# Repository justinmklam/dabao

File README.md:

# dabao

打包 (dǎ bāo or daa2 baau1), which means to take out (food) in Chinese, is a wireless, portable 36-key keyboard with a thumb trackpoint, designed for maximum flexibility and convenience.

> 
> <sub>Keyboard can be used as a unibody...</sub>
>
> 
> <sub>... or as a split!</sub>

## Design Rationale

I found that split keyboards can be cumbersome when I’m not working at a desk. Managing two independent halves (as well as a laptop) while moving between coworking spaces, cafés, or even working from the couch quickly becomes unwieldy, and I thought there had to be a better way.

This project explores a keyboard that can seamlessly switch between a unibody form factor (easy to pick up and carry) and a fully split configuration when there's space for a full ergonomic setup. An integrated pointing device is included to reduce the need for external peripherals, making it truly portable.

Albeit unconventional, the trackpoint is positioned under the thumb to:

- Enable the use of hotswap sockets while keeping the overall keyboard height low
- Eliminate the need to modify keycaps for trackpoint clearance
- Allow the fingers to remain on the home row during pointing tasks

In practice, using the thumb instead of the index finger feels functionally similar. After a short adjustment period, I personally haven't experienced a meaningful loss in accuracy or precision.

## Features

- **Unibody or Split:** Unique magnetic 4-pin connector allows the keyboard to be used as a single unibody or split into two halves via a USB-C cable. Use unibody mode on the go, and split mode at your desk!
- **Single Microcontroller:** Uses one microcontroller and a GPIO expander, eliminating the need for two controllers or batteries to reduce costs and avoid managing uneven battery discharge.
- **Integrated Trackpoint:** For convenient and precise cursor control.
- **Reversible PCB:** Keeps ordering PCBs affordable. Also enables the trackpoint to be installed on the left or right side.
- **Wireless:** Wireless operation (between the host computer) for portability.
- **Hotswap Switches:** Supports Choc V1 or V2 switches. Can also be soldered directly if desired.

## Firmware

See [zmk-config](https://github.com/justinmklam/zmk-config).

## Case

*Coming soon!* - The case will make the magnetic interface more robust, which will allow the keyboard to be lifted from either side without it collapsing in half. Additional magnets will likely be added to make the connection more secure.

## Build Guide

> [!WARNING]
> This project is provided for educational and experimental purposes only. It is shared "as-is," without any warranty of any kind, express or implied, including but not limited to the warranties of merchantability or fitness for a particular purpose. By using these files, you acknowledge that you are assuming all risks associated with the assembly, use, and operation of the hardware. The author shall not be liable for any claim, damages, or other liability, whether in an action of contract, tort, or otherwise, arising from, out of, or in connection with the project or the use of these files.

*Coming soon!*

## Acknowledgements

This design was inspired by the following keyboards:

- [TPS42](https://github.com/crehmann/TPS42)
- [duet](https://github.com/zzeneg/duet)
- [Santoku](https://www.reddit.com/r/ErgoMechKeyboards/comments/oisnad/i_made_this_santoku_gen_2_trackpoint_as_a/?chainedPosts=t3_g4m3f6)

Helpful trackpoint resources:

- [infused-kim's Trackpoint Driver](https://github.com/infused-kim/kb_zmk_ps2_mouse_trackpoint_driver) - outdated for the recent versions of zmk, but still a treasure trove of information
- [Jorne Trackpoint Wiki](https://github.com/joric/jorne/wiki/Tracking)
- [TheMK Wiki - TrackPoint Overview](https://wiki.themk.org/index.php/TrackPoint)
- [KBD News - Trackpoint Integration Guide](https://kbd.news/How-to-integrate-a-trackpoint-into-your-keyboard-2447.html)
- [r/Trackpoint_Builders](https://www.reddit.com/r/TrackPoint_Builders/)
- [Trackpoint Builders Discord](https://discord.gg/48gM4jZkW)

## Support

Thank you to my sponsors for making this project possible!

The PCBs for this project were manufactured by **[PCBWay](https://pcbway.com)**. The boards came out clean with good tolerances and had a fast turnaround, especially considering it came from the other side of the world. Recommended if you're looking to prototype or build your own keyboard!

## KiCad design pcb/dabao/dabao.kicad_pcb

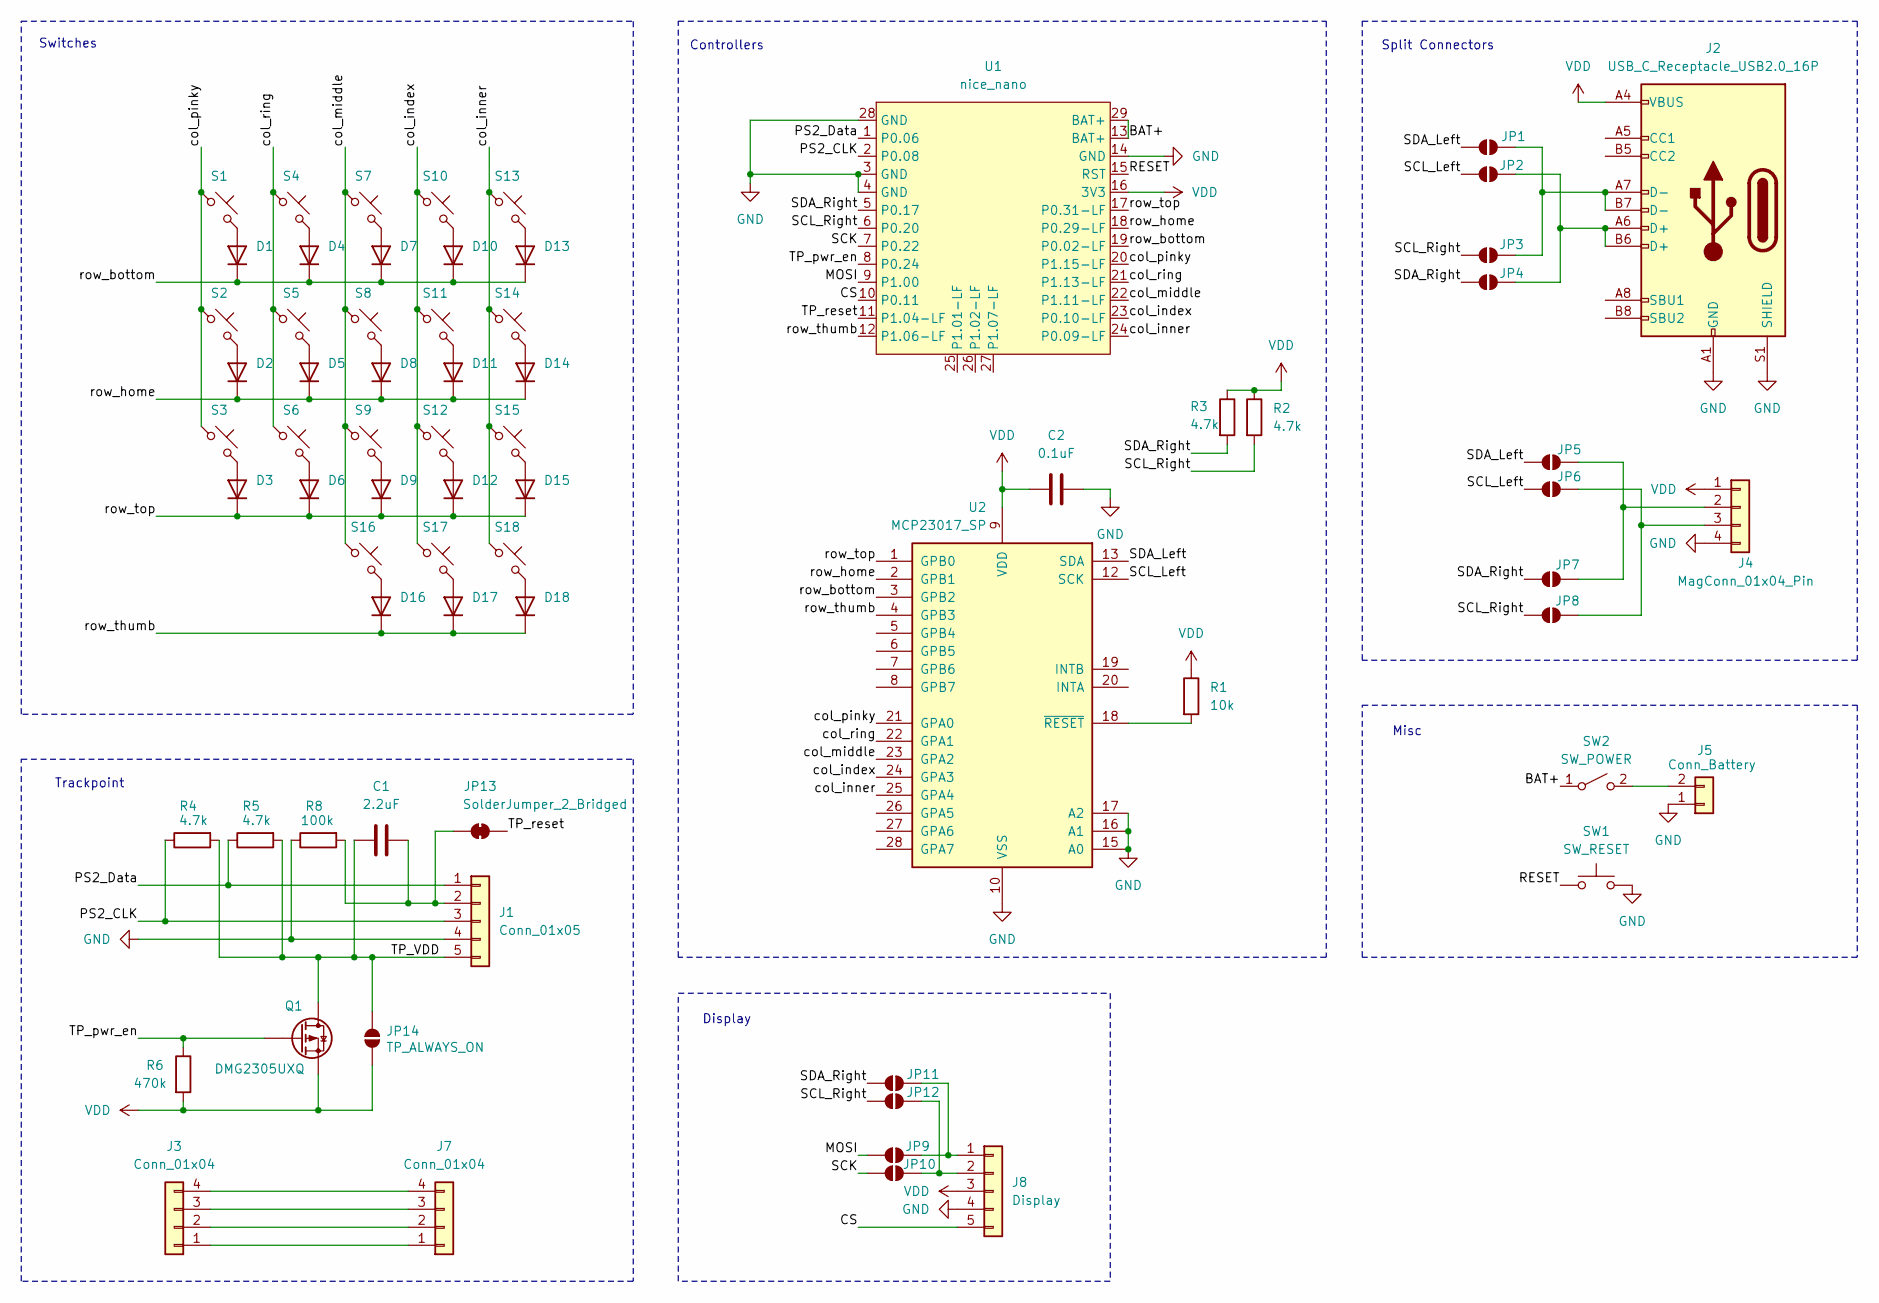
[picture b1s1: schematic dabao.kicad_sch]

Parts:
C1: 2.2uF; C_0805_2012Metric
C2: 0.1uF; C_0805_2012Metric
D1, D2, D3, D4, D5, D6, D7, D8, D9, D10, D11, D12, D13, D14, D15, D16, D17, D18: 1N4148; D_SOD-323_HandSoldering_Reversable
J1: Conn_01x05; TPModule
J2: USB_C_Receptacle_USB2.0_16P; USB_C_Receptacle_GCT_USB4085
J3, J7: Conn_01x04; TPSensorModule_Connector
J4: MagConn_01x04_Pin; PinMagnetic_1x04_P2.54mm
J5: Conn_Battery; JST_PH_S2B-PH-K_1x02_P2.00mm_Horizontal
J8: Display; PinHeader_1x05_P2.54mm_Vertical
JP1, JP2, JP3, JP4, JP5, JP6, JP7, JP8, JP9, JP10, JP11, JP12: SolderJumper_2_Open; SolderJumper-2_P1.3mm_Open_TrianglePad1.0x1.5mm
JP13: SolderJumper_2_Bridged; SolderJumper-2_P1.3mm_Bridged_Pad1.0x1.5mm
JP14: TP_ALWAYS_ON; SolderJumper-2_P1.3mm_Open_TrianglePad1.0x1.5mm
Q1: DMG2305UXQ
R1: 10k; R_0805_2012Metric
R2, R3, R4, R5: 4.7k; R_0805_2012Metric
R6: 470k; R_0805_2012Metric
R8: 100k; R_0805_2012Metric
S1, S2, S3, S4, S5, S6, S7, S8, S9, S10, S11, S12, S13, S14, S15, S16, S17, S18: choc_v1_SW_HS; Kailh_socket_PG1350_optional_reversible.kicad_mod
SW1: SW_RESET; SW_Push_SPST_NO_Alps_SKRK
SW2: SW_POWER; SW_MSK12C02-HB
U1: nice_nano; nice_nano_AH_USBup
U2: MCP23017_SP; SOIC-28W_7.5x17.9mm_P1.27mm

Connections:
/BAT+: SW2.1 (A), U1.13 (BAT+), U1.29 (BAT+)
/CS: J8.5, U1.10 (P0.11)
/MOSI: JP9.1 (A), U1.9 (P1.00)
/PS2_CLK: J1.3, R4.1, U1.2 (P0.08)
/PS2_Data: J1.1, R5.1, U1.1 (P0.06)
/RESET: SW1.1, U1.15 (RST)
/SCK: JP10.1 (A), U1.7 (P0.22)
/SCL_Left: JP2.1 (A), JP6.1 (A), U2.12 (SCK)
/SCL_Right: JP3.1 (A), JP8.1 (A), JP12.1 (A), R2.2, U1.6 (P0.20)
/SDA_Left: JP1.1 (A), JP5.1 (A), U2.13 (SDA)
/SDA_Right: JP4.1 (A), JP7.1 (A), JP11.1 (A), R3.2, U1.5 (P0.17)
/TP_VDD: C1.1, J1.5, JP14.2 (B), Q1.D, R4.2, R5.2
/TP_pwr_en: Q1.G, R6.1, U1.8 (P0.24)
/TP_reset: JP13.2 (B), U1.11 (P1.04-LF)
/col_index: S10.1, S11.1, S12.1, S17.1, U1.23 (P0.10-LF), U2.24 (GPA3)
/col_inner: S13.1, S14.1, S15.1, S18.1, U1.24 (P0.09-LF), U2.25 (GPA4)
/col_middle: S7.1, S8.1, S9.1, S16.1, U1.22 (P1.11-LF), U2.23 (GPA2)
/col_pinky: S1.1, S2.1, S3.1, U1.20 (P1.15-LF), U2.21 (GPA0)
/col_ring: S4.1, S5.1, S6.1, U1.21 (P1.13-LF), U2.22 (GPA1)
/row_bottom: D1.1 (K), D4.1 (K), D7.1 (K), D10.1 (K), D13.1 (K), U1.19 (P0.02-LF), U2.3 (GPB2)
/row_home: D2.1 (K), D5.1 (K), D8.1 (K), D11.1 (K), D14.1 (K), U1.18 (P0.29-LF), U2.2 (GPB1)
/row_thumb: D16.1 (K), D17.1 (K), D18.1 (K), U1.12 (P1.06-LF), U2.4 (GPB3)
/row_top: D3.1 (K), D6.1 (K), D9.1 (K), D12.1 (K), D15.1 (K), U1.17 (P0.31-LF), U2.1 (GPB0)
GND: C2.2, J1.4, J2.A1 (GND), J2.A12 (GND), J2.B1 (GND), J2.B12 (GND), J2.S1 (SHIELD), J4.4, J5.1, J8.4, R8.1, SW1.2, U1.3 (GND), U1.4 (GND), U1.14 (GND), U1.28 (GND), U2.10 (VSS), U2.15 (A0), U2.16 (A1), U2.17 (A2)
unnamed: D1.2 (A), S1.2
unnamed: D2.2 (A), S2.2
unnamed: D3.2 (A), S3.2
unnamed: D4.2 (A), S4.2
unnamed: D5.2 (A), S5.2
unnamed: D6.2 (A), S6.2
unnamed: D7.2 (A), S7.2
unnamed: D8.2 (A), S8.2
unnamed: D9.2 (A), S9.2
unnamed: D10.2 (A), S10.2
unnamed: D11.2 (A), S11.2
unnamed: D12.2 (A), S12.2
unnamed: D13.2 (A), S13.2
unnamed: D14.2 (A), S14.2
unnamed: D15.2 (A), S15.2
unnamed: D16.2 (A), S16.2
unnamed: D17.2 (A), S17.2
unnamed: D18.2 (A), S18.2
unnamed: C1.2, J1.2, JP13.1 (A), R8.2
unnamed: J3.1, J7.1
unnamed: J3.2, J7.2
unnamed: J3.3, J7.3
unnamed: J3.4, J7.4
unnamed: J4.2, JP5.2 (B), JP7.2 (B)
unnamed: J4.3, JP6.2 (B), JP8.2 (B)
unnamed: J5.2, SW2.2 (B)
unnamed: J8.1, JP9.2 (B), JP11.2 (B)
unnamed: J8.2, JP10.2 (B), JP12.2 (B)
unnamed: J2.A7 (D-), J2.B7 (D-), JP1.2 (B), JP3.2 (B)
unnamed: J2.A6 (D+), J2.B6 (D+), JP2.2 (B), JP4.2 (B)
unnamed: R1.2, U2.18 (~RESET)
VDD: C2.1, J2.A4 (VBUS), J2.A9 (VBUS), J2.B4 (VBUS), J2.B9 (VBUS), J4.1, J8.3, JP14.1 (A), Q1.S, R1.1, R2.1, R3.1, R6.2, U1.16 (3V3), U2.9 (VDD)

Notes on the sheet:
Misc
Display
Trackpoint
Split Connectors
Controllers
Switches

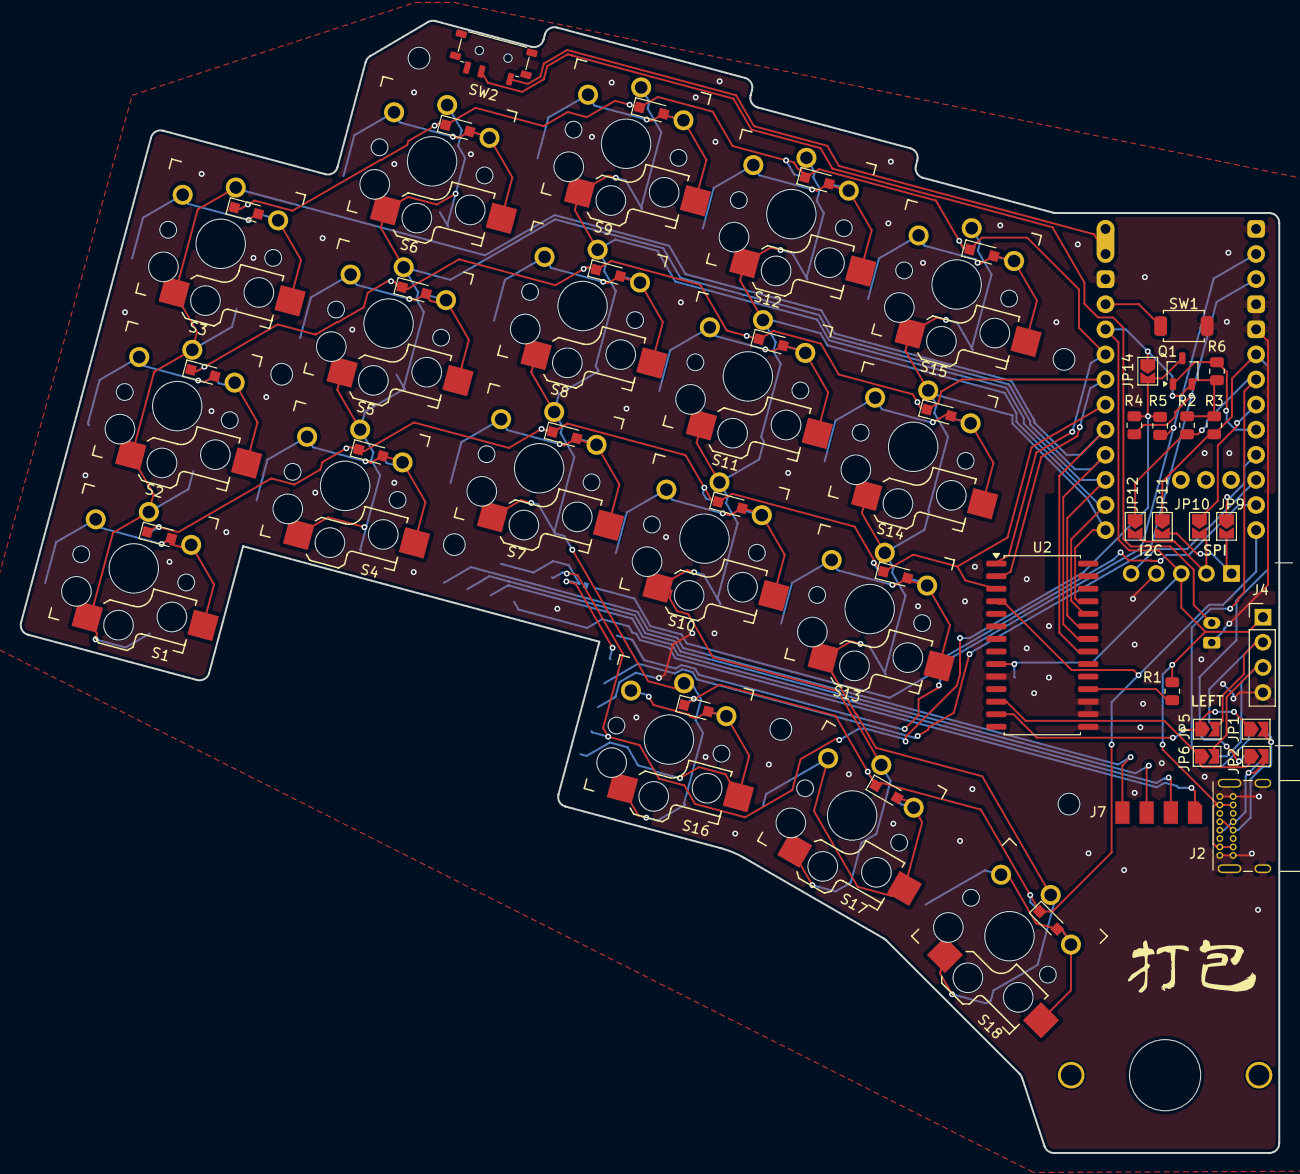
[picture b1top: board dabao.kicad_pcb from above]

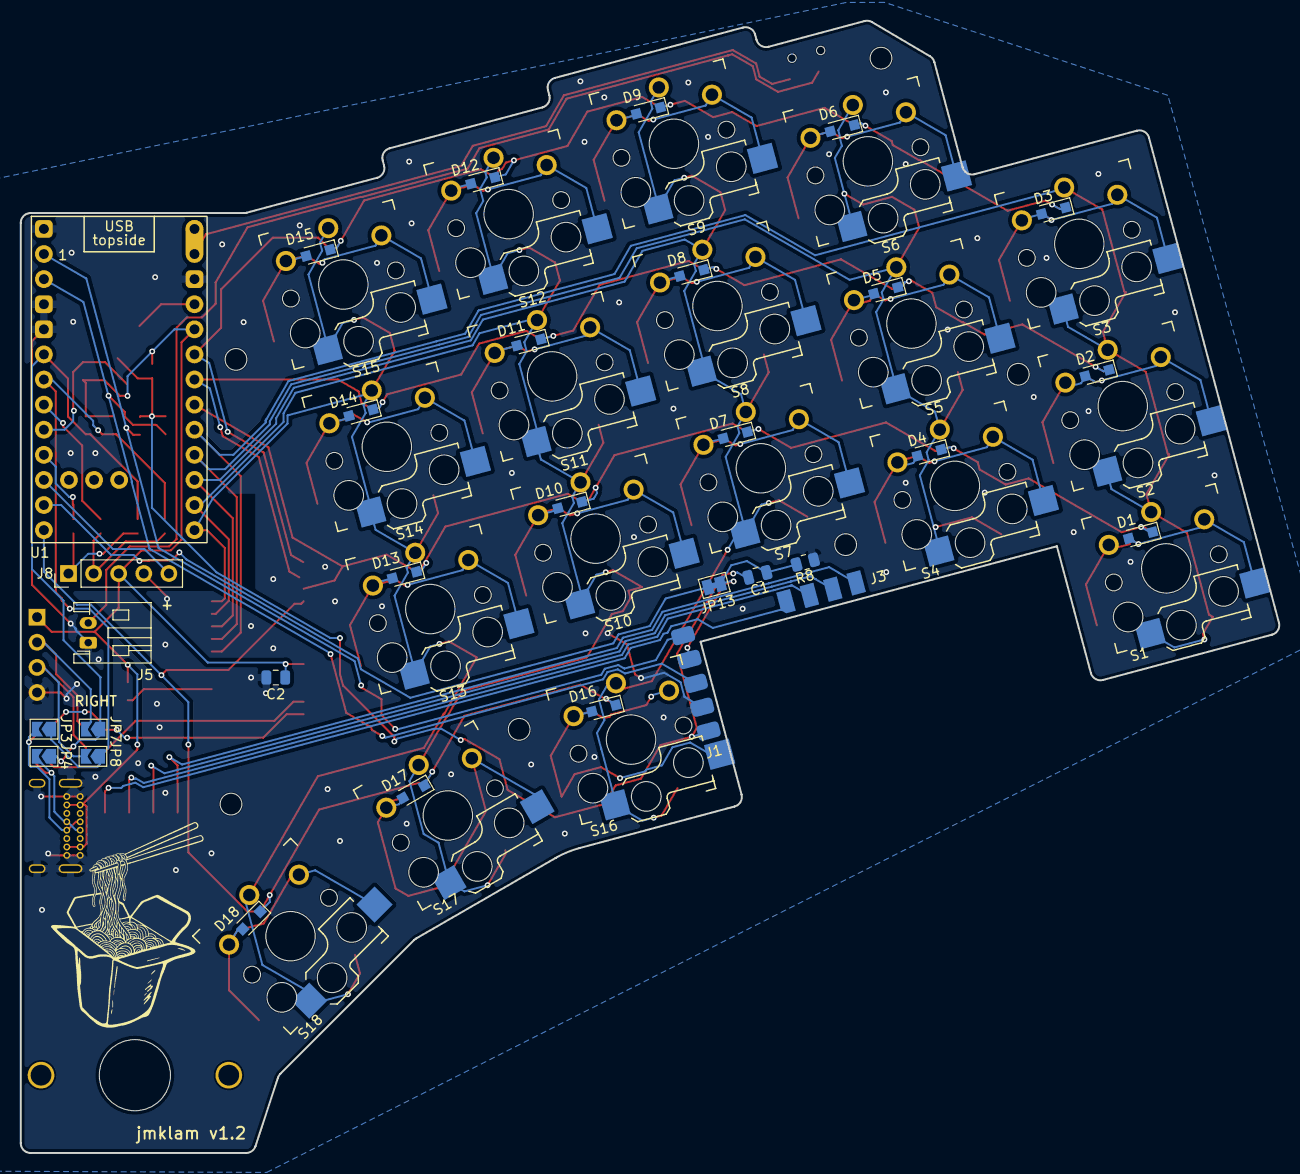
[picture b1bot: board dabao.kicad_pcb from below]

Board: 2 copper layers, 127.4 x 114.6 mm, 71 parts (49 on the bottom side), 56 nets.

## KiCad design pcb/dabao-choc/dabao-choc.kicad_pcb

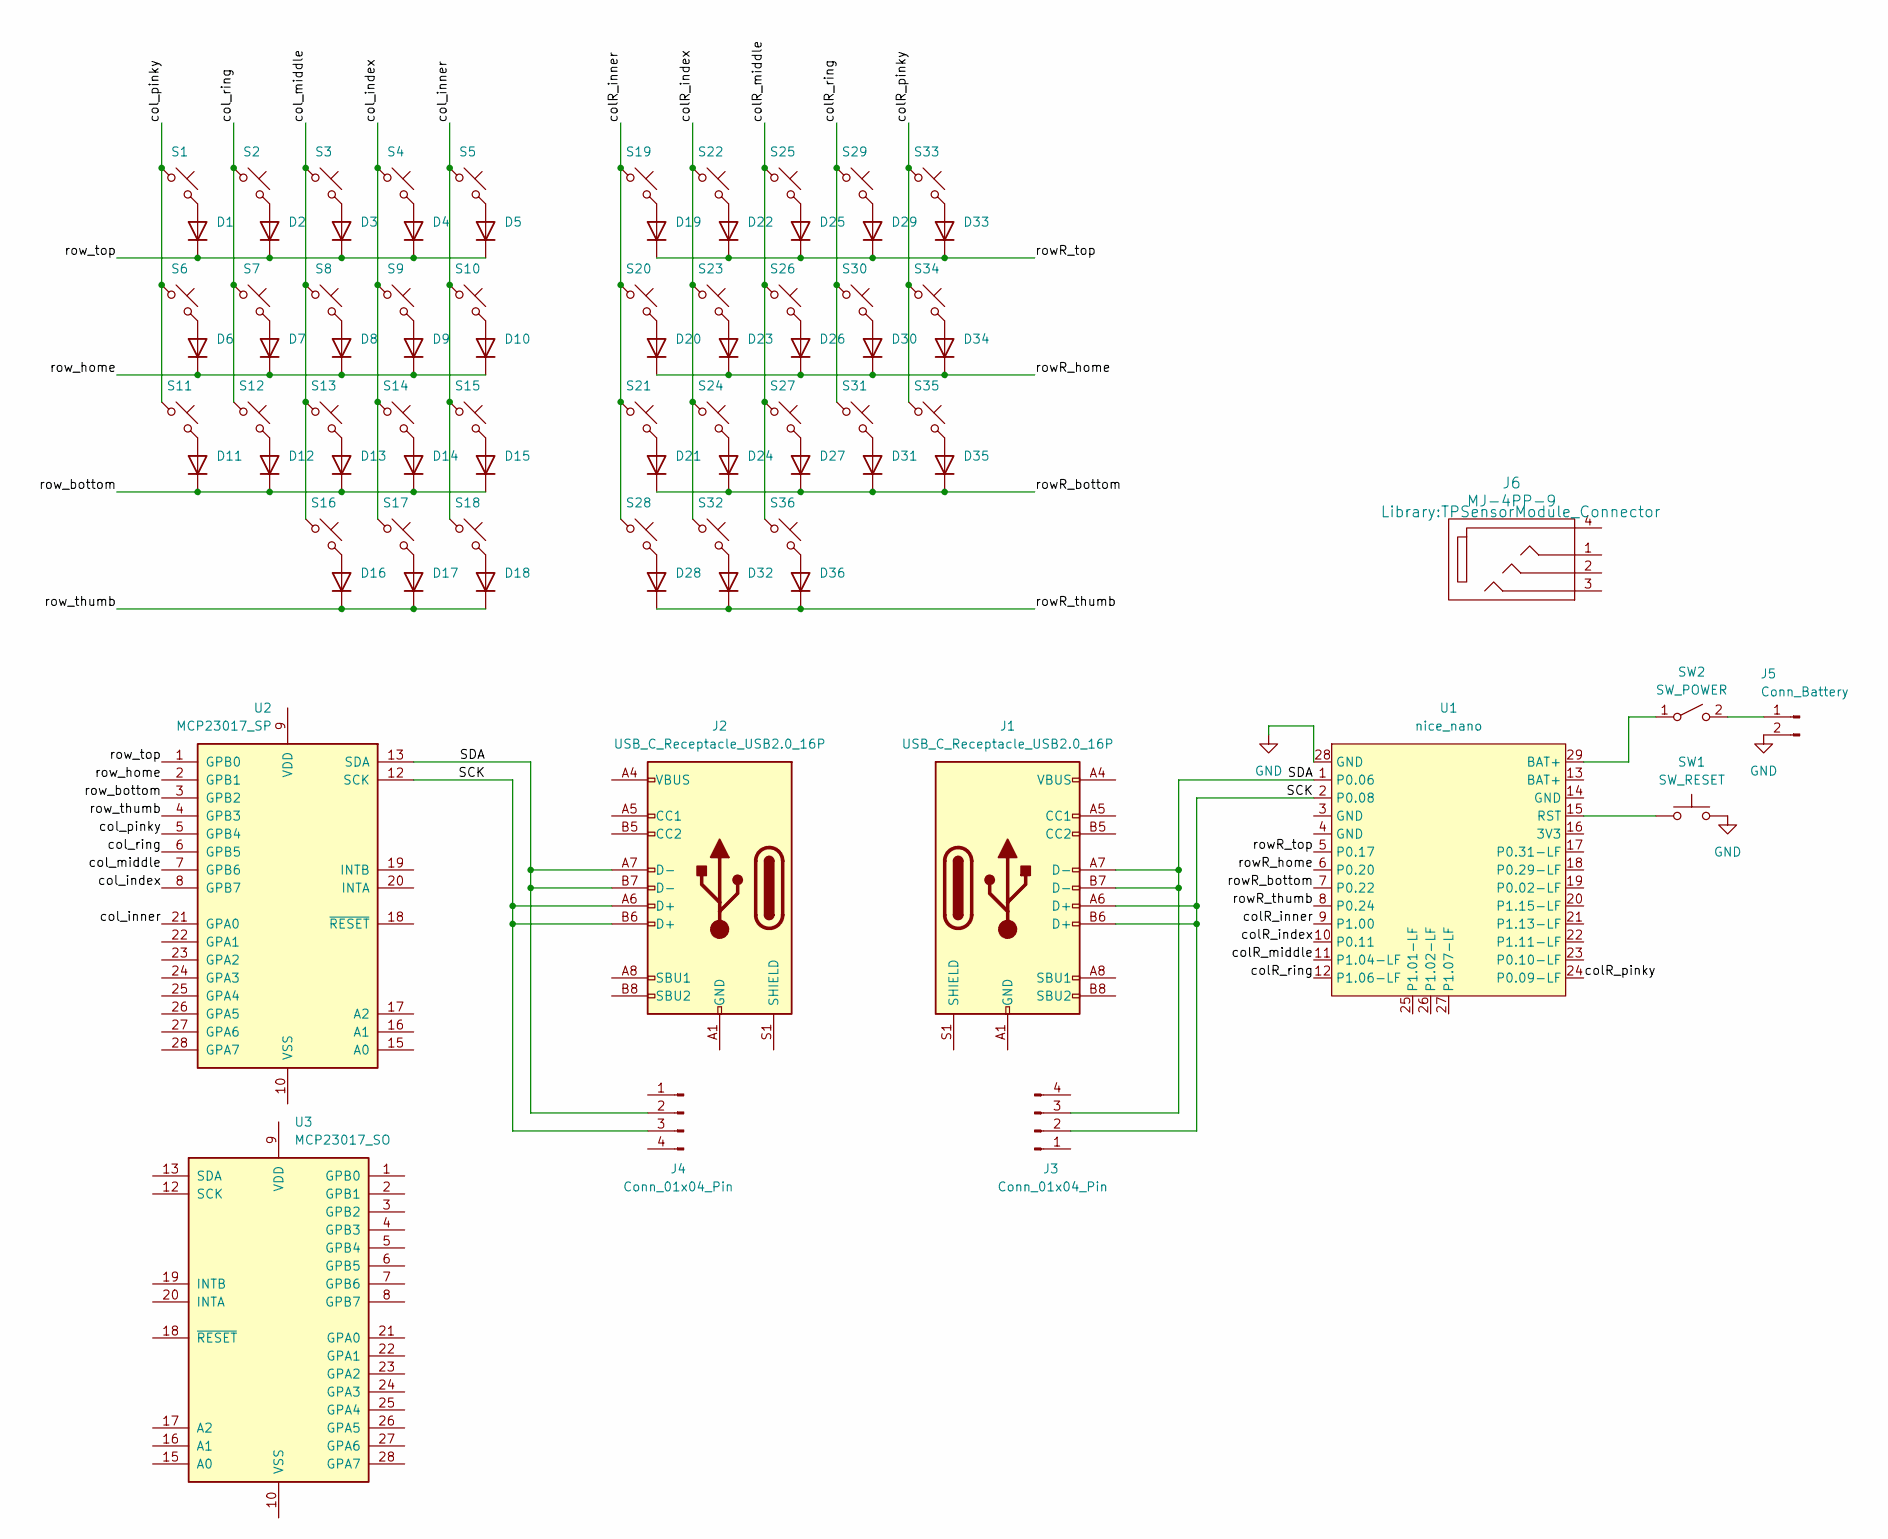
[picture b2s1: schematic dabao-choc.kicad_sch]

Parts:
D1, D2, D3, D4, D5, D6, D7, D8, D9, D10, D11, D12, D13, D14, D15, D16, D17, D18, D19, D20, D21, D22, D23, D24, D25, D26, D27, D28, D29, D30, D31, D32, D33, D34, D35, D36: 1N4148; D_DO-35_SOD27_P7.62mm_Horizontal
J1, J2: USB_C_Receptacle_USB2.0_16P; USB_C_Receptacle_GCT_USB4085
J3, J4: Conn_01x04_Pin; PinMagnetic_1x04_P2.54mm
J5: Conn_Battery; JST_EH_S2B-EH_1x02_P2.50mm_Horizontal
J6: MJ-4PP-9; TPSensorModule_Connector
S1, S2, S3, S4, S5, S6, S7, S8, S9, S10, S11, S12, S13, S14, S15, S16, S17, S18, S19, S20, S21, S22, S23, S24, S25, S26, S27, S28, S29, S30, S31, S32, S33, S34, S35, S36: choc_v1_SW_HS; SW_choc_v1_HS_CPG135001S30_1u
SW1: SW_RESET; SW_Push_SPST_NO_Alps_SKRK
SW2: SW_POWER; SW_MSK12C02-HB
U1: nice_nano; nice_nano_AH_USBup
U2: MCP23017_SP; DIP-28_W7.62mm
U3: MCP23017_SO; SOIC-28W_7.5x17.9mm_P1.27mm

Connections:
/colR_index: S22.1, S23.1, S24.1, S32.1, U1.10 (P0.11)
/colR_inner: S19.1, S20.1, S21.1, S28.1, U1.9 (P1.00)
/colR_middle: S25.1, S26.1, S27.1, S36.1, U1.11 (P1.04-LF)
/colR_pinky: S33.1, S34.1, S35.1, U1.24 (P0.09-LF)
/colR_ring: S29.1, S30.1, S31.1, U1.12 (P1.06-LF)
/col_index: S4.1, S9.1, S14.1, S17.1, U2.8 (GPB7)
/col_inner: S5.1, S10.1, S15.1, S18.1, U2.21 (GPA0)
/col_middle: S3.1, S8.1, S13.1, S16.1, U2.7 (GPB6)
/col_pinky: S1.1, S6.1, S11.1, U2.5 (GPB4)
/col_ring: S2.1, S7.1, S12.1, U2.6 (GPB5)
/rowR_bottom: D21.1 (K), D24.1 (K), D27.1 (K), D31.1 (K), D35.1 (K), U1.7 (P0.22)
/rowR_home: D20.1 (K), D23.1 (K), D26.1 (K), D30.1 (K), D34.1 (K), U1.6 (P0.20)
/rowR_thumb: D28.1 (K), D32.1 (K), D36.1 (K), U1.8 (P0.24)
/rowR_top: D19.1 (K), D22.1 (K), D25.1 (K), D29.1 (K), D33.1 (K), U1.5 (P0.17)
/row_bottom: D11.1 (K), D12.1 (K), D13.1 (K), D14.1 (K), D15.1 (K), U2.3 (GPB2)
/row_home: D6.1 (K), D7.1 (K), D8.1 (K), D9.1 (K), D10.1 (K), U2.2 (GPB1)
/row_thumb: D16.1 (K), D17.1 (K), D18.1 (K), U2.4 (GPB3)
/row_top: D1.1 (K), D2.1 (K), D3.1 (K), D4.1 (K), D5.1 (K), U2.1 (GPB0)
GND: J5.2, SW1.2, U1.28 (GND)
unnamed: D1.2 (A), S1.2
unnamed: D2.2 (A), S2.2
unnamed: D3.2 (A), S3.2
unnamed: D4.2 (A), S4.2
unnamed: D5.2 (A), S5.2
unnamed: D6.2 (A), S6.2
unnamed: D7.2 (A), S7.2
unnamed: D8.2 (A), S8.2
unnamed: D9.2 (A), S9.2
unnamed: D10.2 (A), S10.2
unnamed: D11.2 (A), S11.2
unnamed: D12.2 (A), S12.2
unnamed: D13.2 (A), S13.2
unnamed: D14.2 (A), S14.2
unnamed: D15.2 (A), S15.2
unnamed: D16.2 (A), S16.2
unnamed: D17.2 (A), S17.2
unnamed: D18.2 (A), S18.2
unnamed: D19.2 (A), S19.2
unnamed: D20.2 (A), S20.2
unnamed: D21.2 (A), S21.2
unnamed: D22.2 (A), S22.2
unnamed: D23.2 (A), S23.2
unnamed: D24.2 (A), S24.2
unnamed: D25.2 (A), S25.2
unnamed: D26.2 (A), S26.2
unnamed: D27.2 (A), S27.2
unnamed: D28.2 (A), S28.2
unnamed: D29.2 (A), S29.2
unnamed: D30.2 (A), S30.2
unnamed: D31.2 (A), S31.2
unnamed: D32.2 (A), S32.2
unnamed: D33.2 (A), S33.2
unnamed: D34.2 (A), S34.2
unnamed: D35.2 (A), S35.2
unnamed: D36.2 (A), S36.2
unnamed: J1.A1 (GND), J1.A12 (GND), J1.B1 (GND), J1.B12 (GND)
unnamed: J1.A4 (VBUS), J1.A9 (VBUS), J1.B4 (VBUS), J1.B9 (VBUS)
unnamed: J2.A1 (GND), J2.A12 (GND), J2.B1 (GND), J2.B12 (GND)
unnamed: J2.A4 (VBUS), J2.A9 (VBUS), J2.B4 (VBUS), J2.B9 (VBUS)
unnamed: J5.1, SW2.2 (B)
unnamed: SW2.1 (A), U1.29 (BAT+)
unnamed: SW1.1, U1.15 (RST)

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
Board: 2 copper layers, 93 parts (76 on the bottom side), 66 nets, no tracks yet.

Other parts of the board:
MH1, MH2, MH3, MH4, MH5, MH6, MH7, MH8, MH9, MH10: mounting_hole_npth

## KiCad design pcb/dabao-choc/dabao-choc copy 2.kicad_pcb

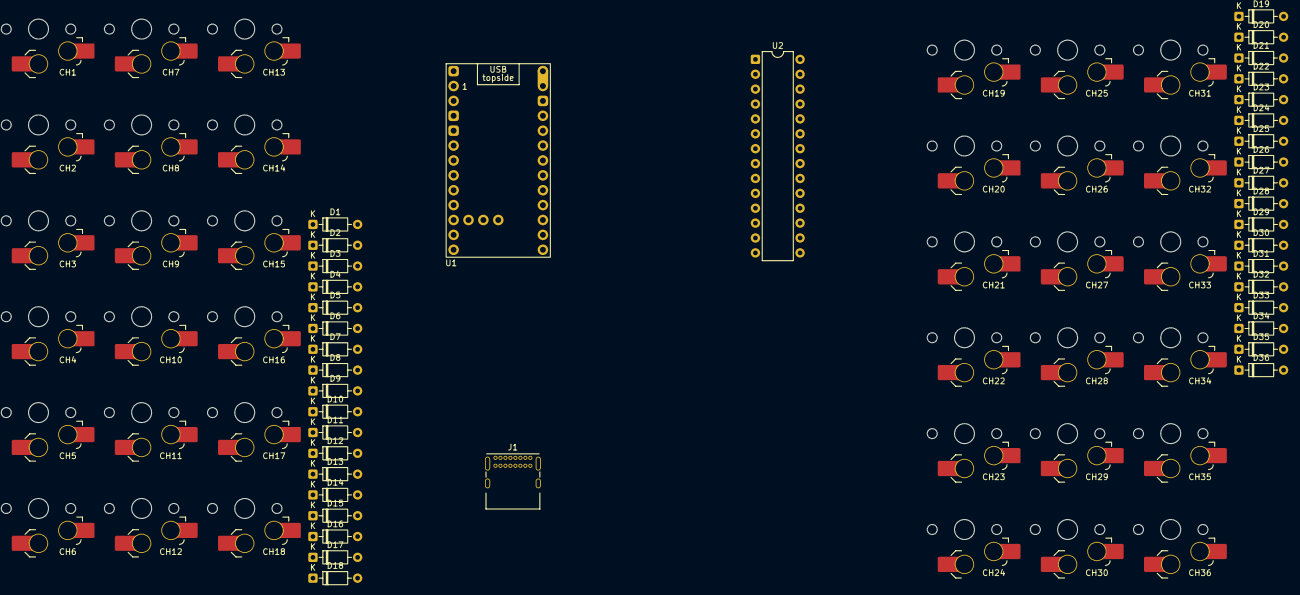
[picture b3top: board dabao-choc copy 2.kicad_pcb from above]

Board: 2 copper layers, 75 parts (0 on the bottom side), 56 nets, no tracks yet.

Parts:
CH1, CH2, CH3, CH4, CH5, CH6, CH7, CH8, CH9, CH10, CH11, CH12, CH13, CH14, CH15, CH16, CH17, CH18, CH19, CH20, CH21, CH22, CH23, CH24, CH25, CH26, CH27, CH28, CH29, CH30, CH31, CH32, CH33, CH34, CH35, CH36: choc_v1_SW_HS; SW_choc_v1_HS_CPG135001S30_1u
D1, D2, D3, D4, D5, D6, D7, D8, D9, D10, D11, D12, D13, D14, D15, D16, D17, D18, D19, D20, D21, D22, D23, D24, D25, D26, D27, D28, D29, D30, D31, D32, D33, D34, D35, D36: 1N4148; D_DO-35_SOD27_P7.62mm_Horizontal
J1: USB_C_Receptacle_USB2.0_16P; USB_C_Receptacle_GCT_USB4085
U1: nice_nano; nice_nano_AH_USBup
U2: MCP23017_SP; DIP-28_W7.62mm

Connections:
/col_index: CH4.1, CH9.1, CH14.1, CH17.1
/col_inner: CH5.1, CH10.1, CH15.1, CH18.1
/col_middle: CH3.1, CH8.1, CH13.1, CH16.1
/col_pinky: CH1.1, CH6.1, CH11.1
/col_ring: CH2.1, CH7.1, CH12.1
/row_bottom: D11.1 (K), D12.1 (K), D13.1 (K), D14.1 (K), D15.1 (K)
/row_home: D6.1 (K), D7.1 (K), D8.1 (K), D9.1 (K), D10.1 (K)
/row_thumb: D16.1 (K), D17.1 (K), D18.1 (K)
/row_top: D1.1 (K), D2.1 (K), D3.1 (K), D4.1 (K), D5.1 (K)
unnamed: CH19.1, CH20.1, CH21.1
unnamed: CH22.1, CH23.1, CH24.1
unnamed: CH25.1, CH26.1, CH27.1, CH28.1
unnamed: CH29.1, CH30.1, CH31.1, CH32.1
unnamed: CH33.1, CH34.1, CH35.1, CH36.1
unnamed: CH1.2, D1.2 (A)
unnamed: CH2.2, D2.2 (A)
unnamed: CH3.2, D3.2 (A)
unnamed: CH4.2, D4.2 (A)
unnamed: CH5.2, D5.2 (A)
unnamed: CH6.2, D6.2 (A)
unnamed: CH7.2, D7.2 (A)
unnamed: CH8.2, D8.2 (A)
unnamed: CH9.2, D9.2 (A)
unnamed: CH10.2, D10.2 (A)
unnamed: CH11.2, D11.2 (A)
unnamed: CH12.2, D12.2 (A)
unnamed: CH13.2, D13.2 (A)
unnamed: CH14.2, D14.2 (A)
unnamed: CH15.2, D15.2 (A)
unnamed: CH16.2, D16.2 (A)
unnamed: CH17.2, D17.2 (A)
unnamed: CH18.2, D18.2 (A)
unnamed: CH19.2, D19.2 (A)
unnamed: D19.1 (K), D22.1 (K), D25.1 (K), D29.1 (K), D33.1 (K)
unnamed: CH20.2, D20.2 (A)
unnamed: D20.1 (K), D23.1 (K), D26.1 (K), D30.1 (K), D34.1 (K)
unnamed: CH21.2, D21.2 (A)
unnamed: D21.1 (K), D24.1 (K), D27.1 (K), D31.1 (K), D35.1 (K)
unnamed: CH22.2, D22.2 (A)
unnamed: CH23.2, D23.2 (A)
unnamed: CH24.2, D24.2 (A)
unnamed: CH25.2, D25.2 (A)
unnamed: CH26.2, D26.2 (A)
unnamed: CH27.2, D27.2 (A)
unnamed: CH28.2, D28.2 (A)
unnamed: D28.1 (K), D32.1 (K), D36.1 (K)
unnamed: CH29.2, D29.2 (A)
unnamed: CH30.2, D30.2 (A)
unnamed: CH31.2, D31.2 (A)
unnamed: CH32.2, D32.2 (A)
unnamed: CH33.2, D33.2 (A)
unnamed: CH34.2, D34.2 (A)
unnamed: CH35.2, D35.2 (A)
unnamed: CH36.2, D36.2 (A)
unnamed: J1.A1 (GND), J1.A12 (GND), J1.B1 (GND), J1.B12 (GND)
unnamed: J1.A4 (VBUS), J1.A9 (VBUS), J1.B4 (VBUS), J1.B9 (VBUS)

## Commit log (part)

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2025-10-09 Start of pcb design
2025-10-09 Add trackpoint parts
2025-10-11 Make reversible pcb
2025-10-12 Update layout
2025-10-12 Clean up schematic
2025-10-13 Fix connectors in layout, add board outline, start routing
2025-10-13 Add missing pullups on ps2 lines
2025-10-25 Move trackpoint to thumb, routing
2025-10-25 Finish routing
2025-10-25 Update routing
2025-10-26 Update pcb outline, final-ish drc checks
2025-10-26 Add nets, tweak layout
2025-10-29 Add logo, update library path
2025-10-30 Add makefile and kicad export targets
2025-11-22 Updates to models
2025-11-22 Add exports
2026-01-10 Update outline for mounting holes
2026-02-06 Cleanup
2026-02-09 Add link to zmk-config to README
2026-02-09 Add case notes and link to infused-kim's driver to README
2026-04-22 Revert "Update outline for mounting holes"
    This reverts commit 8c40ebd10364a523e89f308933ebed6ba8cc3b75.
2026-04-22 PCB updates to fix assembly issues
    Addresses https://github.com/justinmklam/dabao/issues/1
